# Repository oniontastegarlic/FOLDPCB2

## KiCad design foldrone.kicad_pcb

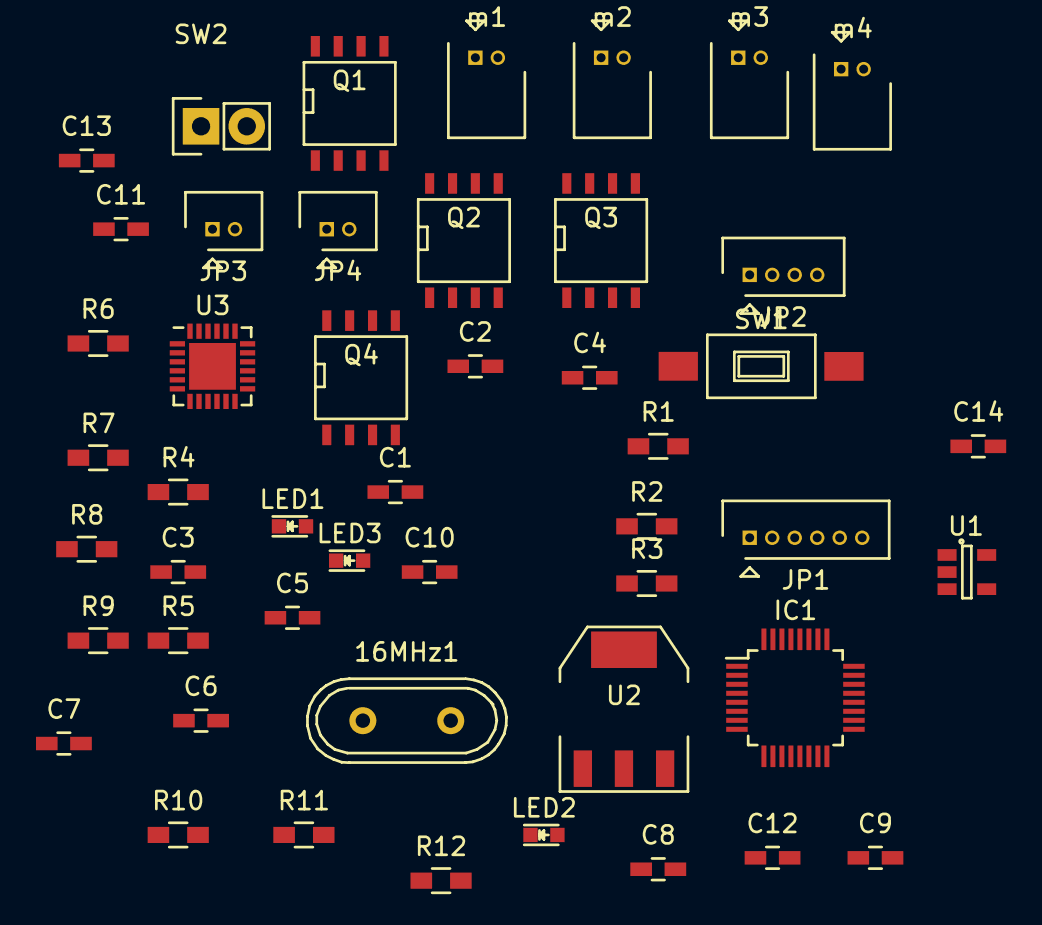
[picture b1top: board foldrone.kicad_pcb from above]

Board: 2 copper layers, 48 parts (0 on the bottom side), 31 nets, no tracks yet.

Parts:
16MHz1: Crystal; Crystal_HC49-U_Vertical
C1, C10: 10μF; C_0603_HandSoldering
C2: 1μF; C_0603_HandSoldering
C3, C6, C7, C12, C13, C14: 0.1μF; C_0603_HandSoldering
C4, C5: 22pF; C_0603_HandSoldering
C8: 4.7μF; C_0603_HandSoldering
C9: 2200pF; C_0603_HandSoldering
C11: 0.01μF; C_0603_HandSoldering
IC1: ATMEGA328P-M; LQFP-32_5x5mm_Pitch0.5mm
JP1: CONN_01X06; Molex_PicoBlade_53047-0610
JP2: CONN_01X04; Molex_PicoBlade_53047-0410
JP3, JP4: CONN_01X02; Molex_PicoBlade_53047-0210
LED1, LED3: Red; LED_0603
LED2: Green; LED_0603
Q1, Q2, Q3, Q4: STS5NF60L; SOIC-8-N
R1, R2, R3, R5, R6, R7, R8, R9: 10K; R_0603_HandSoldering
R4: 330; R_0603_HandSoldering
R10, R11, R12: 4.7K; R_0603_HandSoldering
SW1: Reset; SW_SPST_FSMSM
SW2: LimitSW; Socket_Strip_Straight_1x02
U1: 3.3_lod; SOT-23-5
U2: TLV1117-33IDCY; SOT-223
U3: MPU-6050; QFN-24-1EP_4x4mm_Pitch0.5mm
m1, m2, m3, m4: motor; Molex_PicoBlade_53048-0210

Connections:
+3V3: C10.1, C11.1, C13.1, C14.1, R9.2, R10.1, R11.1, U1.5, U3.8, U3.13
DTR: C3.1, JP1.6
FoldSW: IC1.23, R3.1, SW2.1
GND: C1.2, C2.2, C4.1, C5.1, C6.2, C7.2, C8.2, C9.2, C10.2, C11.2, C12.2, C13.2, C14.2, IC1.3, IC1.5, IC1.21, JP1.1, JP1.2, JP2.3, JP4.2, LED2.1, LED3.1, Q1.1, Q1.2, Q1.3, Q2.1, Q2.2, Q2.3, Q3.1, Q3.2, Q3.3, Q4.1, Q4.2, Q4.3, R1.2, R3.2, R5.1, R6.1, R7.1, R8.1, R12.1, SW1.1, U1.2, U2.1, U3.1, U3.11, U3.18
INT: IC1.32, U3.12
unnamed: 16MHz1.1, C4.2, IC1.7
unnamed: 16MHz1.2, C5.2, IC1.8
unnamed: C3.2, IC1.29, R2.2, SW1.2
unnamed: C6.1, IC1.20
unnamed: C9.1, U3.20
unnamed: C12.1, U3.10
unnamed: IC1.17, R4.2
unnamed: JP3.2, JP4.1
unnamed: LED1.1, R1.1
unnamed: LED2.2, R4.1
unnamed: LED3.2, R9.1
unnamed: Q1.5, Q1.6, Q1.7, Q1.8, m1.2
unnamed: Q2.5, Q2.6, Q2.7, Q2.8, m2.2
unnamed: Q3.5, Q3.6, Q3.7, Q3.8, m3.2
unnamed: Q4.5, Q4.6, Q4.7, Q4.8, m4.2
unnamed: R12.2, U3.9
PWM01: IC1.1, Q1.4, R5.2
PWM02: IC1.9, Q2.4, R6.2
PWM03: IC1.10, Q3.4, R7.2
PWM04: IC1.13, Q4.4, R8.2
RAW: C1.1, JP3.1, U2.3, m1.1, m2.1, m3.1, m4.1
RXD: IC1.30, JP1.4, JP2.2
SCL: IC1.28, R10.2, U3.23
SDA: IC1.27, R11.2, U3.24
TXD: IC1.31, JP1.5, JP2.1
VCC: C2.1, C7.1, C8.1, IC1.4, IC1.6, IC1.18, JP1.3, JP2.4, LED1.2, R2.1, SW2.2, U1.1, U1.3, U2.2
